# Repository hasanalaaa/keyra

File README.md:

<div align="center">

<a href="#readme">
  <picture>
    <source media="(prefers-color-scheme: dark)" srcset="docs/brand/readme/banner-dark.svg">
    
  </picture>
</a>

<h3>Your passwords stay on the device.<br>Keyra types them for you, only when you press its button.</h3>

<a href="https://hasanalaaa.github.io/keyra/">Website</a>&nbsp;&nbsp;·&nbsp;&nbsp;<a href="#how-it-works">How it works</a>&nbsp;&nbsp;·&nbsp;&nbsp;<a href="#quick-start">Quick start</a>&nbsp;&nbsp;·&nbsp;&nbsp;<a href="#security-model">Security</a>&nbsp;&nbsp;·&nbsp;&nbsp;<a href="#hardware">Hardware</a>&nbsp;&nbsp;·&nbsp;&nbsp;<a href="#faq">FAQ</a>&nbsp;&nbsp;·&nbsp;&nbsp;<a href="README.ar.md">العربية</a>
<br><br>

</div>

<picture>
  <source media="(prefers-color-scheme: dark)" srcset="docs/images/hero-dark.jpg">
  
</picture>
<p align="center"><sub>Concept render of a future enclosure. Today Keyra runs on a bare ESP32-S3 dev board: see <a href="#hardware">Hardware</a>.</sub></p>

---

<div dir="rtl">

## بالعربي

**Keyra** خزنة كلمات مرور صغيرة بحجم الـ USB، مبنية على لوحة ESP32-S3. تبقى كلماتك مشفّرة داخل الجهاز، وتديرها من متصفح هاتفك عبر شبكة الجهاز نفسه (`http://keyra.local`)، وعند الحاجة **يكتب Keyra اسم المستخدم وكلمة المرور** في الكمبيوتر كأنه لوحة مفاتيح، **ولكن فقط بعد أن تضغط زر الجهاز بيدك**. لا حساب، لا سحابة، لا إنترنت.

اقرأ الشرح كاملاً بالعربية: **[README.ar.md](README.ar.md)**

</div>

---

## Why Keyra

Most password managers live in the same computer and browser that attackers target. Keyra moves the secret somewhere else.

- **Your vault never lives on the computer.** Nothing is stored or synced there: the computer only sees a keyboard typing the one credential you chose, at the moment you chose. No clipboard, no app to install. (The optional browser extension only *asks* Keyra to type; it never holds a password.)
- **Malware cannot make it type.** Every action needs a physical press of the button on the device. No press, no typing.
- **No cloud, no account, no subscription.** The vault is encrypted on the device and managed over the device's own Wi-Fi. Nothing leaves your desk.
- **Works on any computer.** If it accepts a USB keyboard (a work laptop, a locked-down kiosk, a TV, a console), Keyra works there. Phones, tablets and computers without a free port can pair with it over Bluetooth. Nothing to install.
- **Open and cheap.** MIT licensed firmware for a development board that costs a few dollars. Read it, build it, change it.
- **Easy enough to use daily.** A phone-first app in Arabic and English, built to feel as simple as the password manager on your phone.

Keyra is a convenience-and-isolation device, not a magic shield. Read the [security model](#security-model) for exactly what it does and does not protect.

## How it works

<picture>
  <source media="(prefers-color-scheme: dark)" srcset="docs/brand/readme/how-it-works-dark.svg">
  
</picture>

https://github.com/user-attachments/assets/99ea60c0-720a-45a1-a4e3-737aead647fd

<p align="center"><sub>The press, 8 s: blue while it waits, green once it has typed. Concept render.</sub></p>

1. **Plug in.** Connect Keyra's USB port to the computer. It shows up as a keyboard. (Or pair it once over Bluetooth: see below.)
2. **Join the Wi-Fi.** On your phone, join the network **Keyra-XXXX** and open **http://keyra.local**. (No sign-in sheet pops up; see the [FAQ](#faq).)
3. **Pick an account and what to type.** Unlock with your master passphrase, tap an account, and choose **Username**, **Password**, **Both** or **Code** (2FA).
4. **Press the button.** Click the login field on your computer, press Keyra's button, and it types. The LED flashes green and your phone says **Typed**.

A long press (1.5 seconds) cancels a pending action, or locks the vault if nothing is pending.

```mermaid
sequenceDiagram
    autonumber
    participant P as Your phone
    participant K as Keyra
    participant C as Computer
    P->>K: Type the password of "GitHub" (Wi-Fi, keyra.local)
    Note over K: Armed for 60 s. LED breathes blue.
    Note over K: You press the button
    K->>C: Types it as a USB or Bluetooth keyboard
    K-->>P: Typed
    Note over C: The computer never sees the vault
```

**Bluetooth.** In **Device → Bluetooth**, tap **Pair a new device** and press Keyra's button. For the next 2 minutes Keyra shows up as a keyboard in your phone's, tablet's or computer's Bluetooth settings, and its light pulses cyan; pick it there. After that, **Type into: Auto** types over USB when Keyra is plugged in and otherwise into the Bluetooth device you used last (or pick one in the account sheet). Keyra connects to it only for the action, and the Ready screen tells you which device it is.

## Features

| | |
|---|---|
| **Types like a keyboard** | USB and Bluetooth keyboard. Handles Caps Lock and always releases keys, even on errors. |
| **Any input language** | Tell Keyra each computer's system once: on Windows it types character codes that ignore the active language; on a Mac or iPhone in Arabic it switches to English, types, and switches back. |
| **Updates over Wi-Fi** | **Device → Firmware update** checks GitHub for a new version and installs it after a press of Keyra's button. Only firmware signed with your key is accepted, never an older version, and a version that fails to start rolls back by itself. |
| **Passkeys and security key (USB)** | Keyra is also a FIDO2/U2F security key: create and use passkeys, or use it as a second factor, on sites that support security keys. Press the button when the light double-blinks white. Up to 50 passkeys, listed in **Security → Passkeys**. Optional security key PIN (set from the computer), `hmac-secret` and `credProtect`; passkeys travel in encrypted backups by default. Not FIDO certified; see [docs/FIDO.md](docs/FIDO.md). |
| **Browser extension (optional)** | Keyra Companion for Chrome 116+, Edge, Brave, Opera, Vivaldi and Firefox 128+: a Keyra key in login fields lists the logins for that site, warns before typing a login on another site, fills a strong password from Keyra in sign-up forms and offers **Save to Keyra?** afterwards. Connects with one press; never sees a stored password. See [extension/README.md](extension/README.md). |

<details>
<summary><b>All features</b> (activity log, password health, passkeys, NFC tags, recovery key, generator, import, backup and more)</summary>
<br>

| | |
|---|---|
| **Delete after typing** | Mark an account to delete itself after its password is typed once (or a set number of times): one-time recovery codes and temporary passwords clean themselves up. |
| **Activity log** | **Security → Activity** shows unlocks, wrong passphrase attempts, locks and why, what was typed and when, backups and more. Encrypted on Keyra, never a password, and it can't be cleared from the app. |
| **Password health** | **Security → Password health** lists reused, weak and year-old passwords. Keyra checks them itself; only the list of accounts reaches the phone, never a password. |
| **Bluetooth keyboard** | Bluetooth LE (HID over GATT) for phones, tablets and computers, with the same typing engine. Pairing only opens for 2 minutes after a button press; up to 4 devices; forget any of them from the app. |
| **Android app (optional)** | Keyra for Android (build it from `android/`): autofill suggestions that ask Keyra to type (you still press the button), **Save to Keyra**, and a password generator. It never receives a stored password. See [android/README.md](android/README.md). |
| **Access tokens and AI agents** | **Device → Apps and agents** makes revocable tokens for the Android app, the browser extension or an AI agent. A token can list account names and ask Keyra to type or save, never read a password, and every action still waits for your press. [`tools/keyra-mcp`](tools/keyra-mcp/README.md) lets an MCP client such as Claude Code log in this way. |
| **NFC tags** | **Device → NFC tags** makes stickers: tap one with your phone to get one account ready to type, then press Keyra's button. NTAG 424 DNA tags cannot be cloned. |
| **Recovery key** | Optional. **Security → Recovery kit** makes a key you can print or split into shares; it opens the vault again if you forget the passphrase. |
| **Reveal only after a press** | By default passwords, 2FA secrets and backups reach the phone only after you press Keyra's button, so a stolen browser session reads nothing. |
| **Lock when unplugged** | The vault locks about a second after the USB computer is unplugged or goes to sleep (on by default); optionally also when the Bluetooth device disconnects. |
| **Phone-first web app** | Installable to the home screen. Search, favorites, recents and a strength meter. |
| **Password generator** | Keyra makes new passwords with its hardware random generator: 8 to 128 characters, choose a–z / A–Z / 0–9 / symbols, minimum numbers and symbols, avoid look-alikes. Shows the exact strength in bits. Type it, type it twice (for "confirm password" fields), copy it, or save it. |
| **Password history** | Changing a password keeps the old one: the last 10, with dates, inside the encrypted account. Reveal or copy any of them. |
| **Type any text** | Keyra as a remote keyboard: type up to 256 characters (a Wi-Fi key, a one-off code) after a button press. Keyra forgets the text right after. |
| **Arabic and English** | Full RTL support, auto-detected, switchable at any time. |
| **2FA codes** | Built-in TOTP (SHA-1/256/512, 6 or 8 digits, 30 or 60 seconds). Keyra can type the code too. Add the key by pasting a setup key or `otpauth://` link, or with **Scan QR from a photo**. |
| **Encrypted vault** | PBKDF2-HMAC-SHA256 (about 1.2 s on the device) and per-entry AES-256-GCM. |
| **Unlock rate limiting** | Failed attempts are counted before the key derivation runs; power-cycling does not reset the delay. |
| **Import** | Move from Apple Passwords, Chrome, Bitwarden or 1Password CSV exports, or move 2FA keys from a Google Authenticator export QR. |
| **Encrypted backup** | A passphrase-protected JSON file (format version 3) with accounts, password history and, by default, passkeys; restore by merging or replacing. Older backup files still import. |
| **Physical confirmation** | Typing, passkey and security-key sign-ins, setup, Wi-Fi changes, Bluetooth pairing, firmware installs, saves from apps, deleting an account or passkey, changing the recovery key and factory reset all need a button press. |
| **Home Wi-Fi (optional)** | Keyra can join your home network so `keyra.local` opens from any device on it. Each new browser there is approved once with the button. |
| **Status LED** | Locked, ready, typing, success and error, readable at a glance. |
| **Auto-lock** | Locks after idle (1 to 120 minutes) and zeroizes keys in RAM. |
| **No lock-in** | Standard formats, open protocol ([docs/SPEC.md](docs/SPEC.md)), MIT license. |

</details>

## Screenshots

| Accounts | Ready: press the button | Typed | Security |
|:--:|:--:|:--:|:--:|
| <picture><source media="(prefers-color-scheme: dark)" srcset="web/screenshots/vault-en-dark.png"></picture> | <picture><source media="(prefers-color-scheme: dark)" srcset="web/screenshots/ready-en-dark.png"></picture> | <picture><source media="(prefers-color-scheme: dark)" srcset="web/screenshots/typed-en-dark.png"></picture> | <picture><source media="(prefers-color-scheme: dark)" srcset="web/screenshots/security-en-dark.png"></picture> |

| Type | Device | Search finds settings too | Typing to |
|:--:|:--:|:--:|:--:|
| <picture><source media="(prefers-color-scheme: dark)" srcset="web/screenshots/typing-en-dark.png"></picture> | <picture><source media="(prefers-color-scheme: dark)" srcset="web/screenshots/settings-en-dark.png"></picture> | <picture><source media="(prefers-color-scheme: dark)" srcset="web/screenshots/search-actions-en-dark.png"></picture> | <picture><source media="(prefers-color-scheme: dark)" srcset="web/screenshots/target-en-dark.png"></picture> |

Arabic (right-to-left) and English, light and dark, phone and desktop — all generated from the real app by `npm --prefix web run e2e` (every screen is in [web/screenshots](web/screenshots)).

## Security model

The short version. The full threat model, cryptographic design and rate-limit schedule are in **[SECURITY.md](SECURITY.md)**.

**What Keyra does**

- Encrypts every entry with AES-256-GCM under a random data key, itself protected by a key derived from your passphrase (PBKDF2-HMAC-SHA256, calibrated to about 1.2 s).
- Rate-limits unlock attempts and counts them durably.
- Types only after a physical button press. The computer never gets a storage or network channel from Keyra.
- Signs passkey and security-key requests only while unlocked and after a button press; passkey keys are encrypted with the vault key ([docs/FIDO.md](docs/FIDO.md)).
- Lets a new Bluetooth device pair only during a 2-minute window opened by a button press; the rest of the time only already-paired devices can even connect.
- Keeps decrypted data in RAM only while unlocked, and zeroizes it on lock. It also locks by itself when the USB computer is unplugged or sleeps.
- Shows passwords, 2FA secrets and backups on the phone only after a button press (**Protect reveal**, on by default), so a stolen browser session cannot read them. Deleting an account or passkey, and changing the recovery key, always need a press.
- Gives apps, the browser extension and AI agents arm-only tokens: they can ask Keyra to type or save, never read, and each action needs a press.
- Lets you set a recovery key (optional). Without one, a forgotten passphrase cannot be recovered; with one, it opens the vault again.

**What it does not do (honest limits)**

- **The phone link is plain HTTP over WPA2**, not TLS. Someone who knows your Keyra Wi-Fi password and is on the network can observe the traffic. Keep the Wi-Fi password private.
- **No secure element.** With physical access to the board, an attacker can dump the flash and guess your passphrase offline. Use a long passphrase.
- **Flash encryption and secure boot are optional** and off by default. They are irreversible eFuse steps ([docs/HARDWARE.md](docs/HARDWARE.md#optional-hardening-irreversible)).
- **Keyra has not been independently audited.**
- A keylogger on the computer can still see what Keyra types, as with any keyboard.
- **The security key is not FIDO certified** and uses self attestation; without a secure element its keys are as safe as your passphrase. Unless you set a security key PIN (from the computer), "user verification" means Keyra is unlocked, not a PIN or fingerprint for each sign-in.
- **Bluetooth pairing is "Just Works"** (Keyra has no screen to show a code). Someone within radio range during the 2-minute pairing window could pair their own device, or try to sit in the middle of yours. Pair where you can see who is around, and check the device list afterwards. Details in [SECURITY.md](SECURITY.md#bluetooth).

If you need to report a vulnerability, please use a **private GitHub Security Advisory** as described in [SECURITY.md](SECURITY.md#reporting-a-vulnerability).

## Hardware

<p align="center"><sub>Concept render. The board you can build today is described below.</sub></p>

Keyra runs on a stock **ESP32-S3** dev board with at least **8 MB flash**. No soldering.

| | |
|---|---|
| **Reference board** | ESP32-S3-DevKitC-1 **N16R8** (PSRAM is optional) |
| **Button** | GPIO0 (the board's **BOOT** button) |
| **Status LED** | WS2812 on **GPIO38** (DevKitC-1 v1.1) or **GPIO48** (v1.0), set with `CONFIG_KEYRA_LED_GPIO` |
| **USB** | Plug the board's native **USB** port into the computer (not the UART port) |

Pin details, flashing options and the optional hardening steps: **[docs/HARDWARE.md](docs/HARDWARE.md)**.

### Enclosure

A printable case for the dual USB-C YD-ESP32-S3 board: five parts, a big mechanical button that presses the board's own BOOT switch, a clear ring that carries the LED's light around it, and the Contour debossed in the lid. No screws, no extra electronics. Cable and USB-C dongle versions, the parametric OpenSCAD source and print settings: **[hardware/enclosure](hardware/enclosure)**.

## Quick start

### Option A: flash a prebuilt release

1. Download the release files from the [Releases page](https://github.com/hasanalaaa/keyra/releases): `bootloader.bin`, `partition-table.bin`, `ota_data_initial.bin`, `keyra-firmware.bin`, `flash-offsets.txt` and `SHA256SUMS`.
2. Put the board in download mode (hold **BOOT**, plug in the **USB** port, release **BOOT**), or use the **UART** port, which needs no button.
3. Flash with [esptool](https://docs.espressif.com/projects/esptool/en/latest/) (the offsets are in `flash-offsets.txt`, one of the release files):

```sh
esptool.py --chip esp32s3 -p <PORT> --before default-reset --after hard-reset \
  write_flash --flash-mode dio --flash-size 8MB --flash-freq 80m \
  0x0 bootloader.bin 0x8000 partition-table.bin 0xf000 ota_data_initial.bin 0x20000 keyra-firmware.bin
```

That is needed once. After it, **Device → Firmware update** installs new versions over Wi-Fi (Keyra on your home network): it checks the [Releases page](https://github.com/hasanalaaa/keyra/releases), downloads, verifies the signature and installs after a press of Keyra's button.

### Option B: build from source

You need [ESP-IDF 6.0.x](https://docs.espressif.com/projects/esp-idf/en/stable/esp32s3/get-started/) installed and exported in your shell (CI uses v6.0.2).

```sh
git clone https://github.com/hasanalaaa/keyra.git
cd keyra/firmware

# Release build: plain keyboard, logging off. Recommended for daily use.
idf.py -B build-release -D SDKCONFIG_DEFAULTS="sdkconfig.defaults;sdkconfig.release" build
idf.py -B build-release -p <PORT> flash

# Dev build: adds a USB serial log port and the 1200-baud reboot-to-ROM hook.
idf.py build
idf.py -p <PORT> flash monitor
```

The built web app is committed in `firmware/components/keyra_api/www/`, so you do **not** need Node.js to build the firmware. To rebuild the web app and refresh those files:

```sh
npm --prefix web ci && npm --prefix web run build
```

### First-time setup

1. Plug Keyra's **USB** port into a computer.
2. On your phone, join Wi-Fi **Keyra-XXXX** (the last four characters of the board's address). The factory password is **`keyra1234`**, and it is public. Setup makes you change it.
3. Open **http://keyra.local** (or `http://192.168.4.1`). Tap **Share, then Add to Home Screen** to make it one tap next time.
4. Follow the three steps: choose a **master passphrase** (10 characters or more; longer is better), choose a **new Wi-Fi password**, then **press the button on Keyra** to prove you are holding it.
5. Add accounts, or import a CSV from your current password manager (delete the CSV afterwards, it is unencrypted).

### Home Wi-Fi (optional)

Keyra can also join your home network, so you can open it from any phone or laptop at home without switching Wi-Fi.

1. In **Device → Home Wi-Fi**, turn on **Use home Wi-Fi** and pick your network. Keyra only joins password-protected (WPA2/WPA3) networks.
2. Enter the network's password, tap **Join**, then **press Keyra's button**. The sheet shows **Connected**, Keyra's address on your network and the signal strength.
3. From any device on that network, open **http://keyra.local**. If a device cannot resolve `.local` names, use the address shown in the sheet.
4. The first time each browser unlocks Keyra through the home network, Keyra asks you to **press its button to trust that browser**. Trusted browsers (up to 8) are listed in **Device → Trusted browsers**, where you can remove them. Removing one signs it out.

### Updating

1. Join Keyra to your home Wi-Fi (see above): checking for updates needs the internet.
2. Open **Device → Firmware update** and tap **Check for updates**.
3. If a newer version is listed, tap **Download and install**, then **press Keyra's button** when the sheet asks. Keyra restarts with the new version; unlock it again.

Your accounts stay as they are (the vault has its own storage). Keyra accepts only firmware signed with your release key, never an older version, and if the new version fails to start it goes back to the previous one by itself. Without home Wi-Fi, **Install from a file** takes a downloaded `keyra-firmware.bin`.

### New password for a website

1. On the website's sign-up or change-password page, open Keyra's **Type** tab and tap **Generate password**. Keyra makes a password (20 characters by default; the sheet remembers your settings in this browser).
2. Click the website's first password field, tap **Type twice**, then **press Keyra's button**. Keyra types the password, presses Tab, and types it again into the confirm field.
3. Tap **Save**: **New account** opens a filled-in form, or **Update an account** replaces that account's password. The old password stays in the account's **Password history**.

To type something that isn't saved in Keyra, open the **Type** tab, then **Type text**, enter up to 256 characters, tap **Type it** and press the button. **Type it twice** can put a Tab or an Enter between the two copies.

**Keep Keyra's own Wi-Fi on** is on by default. Turn it off and Keyra's own Wi-Fi switches off about 15 seconds after Keyra joins your home network; it comes back if the home network has been unavailable for 60 seconds, or 30 seconds after power-up if Keyra has not joined by then, so Keyra stays reachable. Keyra has one radio: its own Wi-Fi moves to your home network's channel, and phones joined to it may reconnect once. While home Wi-Fi is connected, Keyra sets its clock from the internet (NTP), so 2FA codes work without a phone having set the time.

### NFC tags

Stick an NFC tag on your desk; tapping it with your phone gets one account ready to type, and you press Keyra's button. The phone must be on Keyra's network (its own Wi-Fi or your home network), and Keyra must be unlocked.

1. In **Device → NFC tags**, tap **New tag**, pick the account, what to type and **Any NFC tag**, tap **Create tag** and press Keyra's button.
2. On iPhone, open **NFC Tools → Write → Add a record → URL**, paste the link Keyra shows (once), tap **Write** and hold the tag near the top of the phone. NXP TagWriter works too.
3. Tap the tag: Safari opens a small Keyra page that says **Press Keyra's button**. Press it and Keyra types.

Anyone who copies a simple tag's link can ask Keyra to type that account (never see it), so your press is still the check. An **NTAG 424 DNA** tag can't be copied: choose it in step 1 and set the keys and SDM offsets Keyra shows in NXP TagWriter. Details: [docs/research/NFC-TAGS.md](docs/research/NFC-TAGS.md).

### Browser extension

1. Build it (`npm --prefix extension ci && npm --prefix extension run build`) and load `extension/dist/chrome` in `chrome://extensions` (Developer mode → **Load unpacked**; Chrome 116+, Edge, Brave, Opera and Vivaldi), or `extension/dist/firefox` in Firefox 128+'s `about:debugging`. Safari is not shipped.
2. Click the Keyra button in the toolbar, enter Keyra's address and click **Connect**. A Keyra tab opens: unlock, tap **Create token** and **press Keyra's button**. The tab closes by itself.
3. On a website, click into the login field and then the small Keyra key: pick the login and **press Keyra's button**. After a sign-up or a password change, the extension asks **Save to Keyra?** or **Update the password?** — again a press.

Only logins for the page's own site are offered; choosing one for another site shows a warning that names both. Install, privacy and permissions: [extension/README.md](extension/README.md).

## Project layout

```
keyra/
├── firmware/                  ESP-IDF 6.0 project (C++17)
│   ├── main/                  app_main: wiring only
│   ├── components/
│   │   ├── keyra_vault/       crypto, encrypted storage, TOTP, backup (host-tested)
│   │   ├── keyra_hid/         typing engine over USB (TinyUSB) or Bluetooth, dev CDC port
│   │   ├── keyra_ble/         Bluetooth LE keyboard (NimBLE, HID over GATT), pairing and bonds
│   │   ├── keyra_fido/        USB security key: CTAPHID, CTAP2 + U2F, passkeys (host-tested)
│   │   ├── keyra_io/          button (GPIO0) and RGB status LED
│   │   ├── keyra_net/         Wi-Fi access point, DNS, mDNS (keyra.local)
│   │   └── keyra_api/         HTTP server, REST API, sessions, pending-action state machine
│   ├── test/host/             host test runner (CMake + ctest, no board needed)
│   ├── partitions.csv         8 MB layout: 2 app slots + LittleFS vault
│   └── sdkconfig.defaults / sdkconfig.release   dev and release profiles
├── web/                       Preact + TypeScript app, built into one gzipped file
├── android/                   Keyra for Android: autofill and save through access tokens (Kotlin)
├── extension/                 Keyra Companion: browser extension (Manifest V3; Chrome, Edge, Brave, Opera, Vivaldi, Firefox)
├── tools/
│   ├── keyra-mcp/             MCP server: lets an AI agent ask Keyra to type a login
│   ├── release.sh             build, sign and publish a release
│   ├── sign_release.sh        sign a firmware image for network updates
│   ├── ci_local.sh            the CI jobs, run locally
│   └── devctl.py, fido_harness.py   flash/reset/log; python-fido2 vs. the FIDO core
├── docs/                      SPEC.md, DESIGN.md, HARDWARE.md, FIDO.md, IMAGE_PROMPTS.md, images/
│   ├── brand/                 logo, colours, type and motion (BRAND.md), README art
│   └── research/              design notes: tokens, NFC tags, host matching, passkey backup, roadmap
└── .github/                   CI, issue and PR templates
```

[docs/SPEC.md](docs/SPEC.md) is the contract between firmware and web app (REST API, behavior, security model). [docs/DESIGN.md](docs/DESIGN.md) is the design system.

## Development

```sh
# Host tests: vault, TOTP, key map, action state machine, FIDO core. No board needed.
# Requires CMake, a C++17 compiler and OpenSSL 3 headers (libssl-dev, or openssl@3 on Homebrew).
cmake -S firmware/test/host -B build/host && cmake --build build/host && ctest --test-dir build/host

# The FIDO core against python-fido2's client and server (fake HID link, no board)
python3 -m venv .venv && .venv/bin/pip install fido2
.venv/bin/python tools/fido_harness.py build/host/keyra_fido/fido_harness

# Web: typecheck and unit tests
npm --prefix web ci
npm --prefix web run typecheck
npm --prefix web test

# Web UI without a board: a mock of the device API (demo passphrase: keyra demo vault)
npm --prefix web run mock

# End-to-end run in a headless browser (Playwright); regenerates the screenshots
npm --prefix web run e2e

# Browser extension: typecheck, unit tests, build, and an end-to-end run in Chromium
npm --prefix extension ci
npm --prefix extension run typecheck && npm --prefix extension test && npm --prefix extension run build
npm --prefix extension run e2e
```

CI runs the host tests, the web checks and both firmware profiles on every push and pull request; `tools/ci_local.sh` runs the same jobs locally. See [CONTRIBUTING.md](CONTRIBUTING.md).

## Roadmap

Ideas, not promises. Priorities follow what real users on real boards report.
The current work plan, with what is done and what comes next, is in [docs/research/ROADMAP.md](docs/research/ROADMAP.md).

- [x] 0.1: encrypted vault, USB typing, phone app (EN/AR), TOTP, import, backup, CI
- [x] 0.2.0: Bluetooth LE keyboard, USB passkeys / FIDO2 + U2F security key, over-the-air firmware updates (signed, with rollback)
- [x] 0.3.0: security key PIN (ClientPIN, separate from the master passphrase), `hmac-secret` and `credProtect`, passkeys in encrypted backups (format version 3)
- [x] 0.3.0: Android app, Keyra Companion browser extension, access tokens and the agent gate (`tools/keyra-mcp`), NFC tap tags
- [x] Board matrix and a prebuilt image for each of seven boards (0.4.5; [docs/HARDWARE.md](docs/HARDWARE.md); hardware-tested so far: YD-ESP32-S3)
- [x] Browser-based flashing for every board from [the website](https://hasanalaaa.github.io/keyra/)
- [x] Printable enclosure ([hardware/enclosure](hardware/enclosure))
- [x] A purpose-built PCB, designed and ready to order: [Keyra Stick](hardware/pcb/keyra-stick) (not yet built)
- [ ] Independent security review (an internal review and its fixes shipped in 0.4.5: [docs/research/SECURITY-REVIEW-2026-10.md](docs/research/SECURITY-REVIEW-2026-10.md))

## FAQ

<details>
<summary><b>Why doesn't my phone show a "sign in to Wi-Fi" popup?</b></summary>

On purpose. Keyra answers your phone's connectivity checks as "online" so the phone joins like any normal network and does not open a cramped captive-portal sheet (which often cannot run the app properly or keep cookies). Just open **http://keyra.local** in your regular browser. If that name does not resolve, use `http://192.168.4.1`.

</details>

<details>
<summary><b>My computer is in Arabic (or another language). Will Keyra type the right characters?</b></summary>

Yes, once Keyra knows the computer's system (Device → Keyboard, Device → Bluetooth per device; iPhones, iPads and Macs are recognised when they pair). On **Windows** it types each character as an Alt code, which comes out the same in every input language. On a **Mac, iPhone or iPad**, set "Its language now" to Arabic under "Type into": Keyra presses Ctrl+Space to switch to English, types, and switches back. On **Android**, set the physical keyboard "Keyra" to English (US) once. No keyboard can *read* a computer's language, which is why Apple hosts need that one tap. Characters a layout cannot type are refused with a clear message, never typed wrong.

</details>

<details>
<summary><b>Can Keyra type into my phone or tablet?</b></summary>

Yes, over Bluetooth. Pair it once from **Device → Bluetooth** (see [How it works](#how-it-works)). iPhone and iPad hide their on-screen keyboard while any Bluetooth keyboard is connected, so by default (**Connect: When typing**, recommended) Keyra connects only for each action: it shows "Connecting to your device…" for a moment, types after your press, and lets go about 20 seconds later. Choose **Always** if you prefer instant typing and do not mind the hidden on-screen keyboard. The account sheet's **Type into** picker chooses USB or a paired device; this browser remembers the choice.

</details>

<details>
<summary><b>I forgot my master passphrase. Can I recover my passwords?</b></summary>

Only with a recovery key you made earlier (**Security → Recovery kit**; make one while you still remember the passphrase). On the unlock screen choose **Use recovery key**, enter it and pick a new passphrase. Without a recovery key, no: that is the point of encryption, and there is no backdoor. You can **erase the device and start over**: on the unlock screen choose **Forgot passphrase?**, then press Keyra's button to confirm. All accounts are deleted. Restore from a backup if you have one.

</details>

<details>
<summary><b>Is it safe to type a password with a button press? What if the wrong window is focused?</b></summary>

The action is armed for 60 seconds and runs once on the press. Click the right field first. A long press cancels.

</details>

<details>
<summary><b>Why HTTP and not HTTPS?</b></summary>

A device on its own network cannot get a certificate that browsers trust without installing something on each phone, and a browser warning teaches people to ignore warnings. The link is protected by WPA2 and a private Wi-Fi password instead. This is a real limit: see [SECURITY.md](SECURITY.md).

</details>

<details>
<summary><b>Can I add a 2FA key from a QR code?</b></summary>

Yes. In the account form, tap **Scan QR from a photo**, then take a photo of the QR or choose a saved picture. The picture is decoded inside your phone's browser; it is never sent to Keyra or anywhere else. Keyra's page is plain HTTP, so browsers do not allow a live camera view there, hence the photo. Plain `otpauth://totp/…` QR codes fill the 2FA field (and the name and user name if they are empty). For Google Authenticator, use **Import**, then **Google Authenticator export**: it lists the accounts in the export QR (several QR codes for big exports, one scan each) and either adds them as new accounts or adds the key to existing accounts that match by name and user name. Keyra only makes time-based codes, so counter-based (HOTP) entries, MD5 and unusual digit counts or periods are rejected or skipped with a message. Delete any photo or screenshot of the QR afterwards: it holds your keys unencrypted.

</details>

<details>
<summary><b>Do I need an internet connection?</b></summary>

No. Keyra creates its own Wi-Fi network, and your phone does not need internet while connected to it (it may keep using mobile data for other apps). If you turn on home Wi-Fi, Keyra uses the internet, on your home network only, for the time (NTP) and to check for and download firmware updates from GitHub when you ask it to, and for nothing else; your vault never leaves the device.

</details>

<details>
<summary><b>Do I still need Keyra's own Wi-Fi once home Wi-Fi works?</b></summary>

Not for everyday use at home: open http://keyra.local on your home network instead. Keyra's own Wi-Fi is still useful. It is how you set Keyra up and how you reach it when the home network is down (with **Keep Keyra's own Wi-Fi on** turned off, it comes back after a minute without the home network). It is also the safer way to unlock on a network you do not fully trust, because traffic on it is visible only to devices that know Keyra's Wi-Fi password (see [SECURITY.md](SECURITY.md#home-wi-fi-optional)). If you never want it while at home, turn **Keep Keyra's own Wi-Fi on** off.

</details>

<details>
<summary><b>Can the computer read my vault?</b></summary>

Keyra presents a keyboard and a security key to the computer. It has no storage interface and no network path to it. The computer sees what gets typed, and it can ask the security key to sign a website's challenge, which needs your button press; it can never read the vault or a key. Over Bluetooth a paired device sees a keyboard, Keyra's name and maker, and a battery level, nothing more.

</details>

<details>
<summary><b>Is Keyra a YubiKey replacement?</b></summary>

No. Keyra can create and use passkeys and act as a security key over USB, and for many personal accounts that works well. But a YubiKey keeps its keys in a secure chip that cannot be read out, is FIDO certified, asks for its PIN on every sign-in, and works over NFC. Keyra has no secure chip (its keys are as safe as your passphrase and the flash encryption setting), is not certified, treats "unlocked" as user verification unless you set an optional security key PIN, and works only by USB (phones need a USB connection). Some sites, mostly corporate ones, refuse uncertified keys. Register a second key or keep another sign-in method on every account. Details in [docs/FIDO.md](docs/FIDO.md).

</details>

<details>
<summary><b>Which passkey sites work?</b></summary>

Any site that accepts a USB security key or "passkey on a security key", in Chrome, Edge, Safari or Firefox on macOS, Windows and Linux. Passkeys need Keyra plugged in and unlocked; keep the phone app handy to unlock it. Encrypted backups carry the passkeys too (Security → "Passkeys in backups", on by default), so a restored Keyra signs in where the old one did.

</details>

<details>
<summary><b>What does it cost?</b></summary>

A compatible ESP32-S3 board is usually a few dollars to about ten.

</details>

## Contributing

Bug reports, hardware test reports, translations and pull requests are welcome. Start with [CONTRIBUTING.md](CONTRIBUTING.md) and the [Code of Conduct](CODE_OF_CONDUCT.md). For security issues, use a private advisory ([SECURITY.md](SECURITY.md)).

## License

[MIT](LICENSE) © 2026 hasanalaaa. Third-party components keep their own licenses (ESP-IDF, TinyUSB, LittleFS, cJSON, Preact). The app and the wordmark use [Readex Pro](https://fonts.google.com/specimen/Readex+Pro) (SIL OFL 1.1). Logo and brand: [docs/brand/BRAND.md](docs/brand/BRAND.md).

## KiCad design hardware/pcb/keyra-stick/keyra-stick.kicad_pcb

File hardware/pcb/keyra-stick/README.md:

# Keyra Stick

Keyra's own board: a 0.8 mm USB-C stick that plugs straight into a computer. One big button, a
ring of eight RGB LEDs around it, the ESP32-S3 module at the far end. Open hardware (MIT), ready to
order fully assembled from JLCPCB with the files in [fab/](fab).

**The illustrated guide** walks through every part, the size, how it works, the schematic, the parts
list, ordering and first power-up: [English](docs/keyra-stick-guide-en.pdf) ·
[العربية](docs/keyra-stick-guide-ar.pdf) (PDF).

> **Status: designed and checked, not yet built.** The schematic passes KiCad's electrical rules
> check, the board passes the design rules check with zero errors and matches the schematic
> exactly, and every fab file is rebuilt from one description by `gen/build.sh`. No board has been
> manufactured or powered yet: if you build one, please report how it went.

## At a glance

| | |
|---|---|
| Size | 53.1 × 18.5 mm board plus the USB-C plug; about 3.2 mm thick with parts (the 2.4 mm module on a 0.8 mm board) |
| Board | 4 layers, 0.8 mm, ENIG, black mask, white silkscreen |
| Layers | top: parts and signals · In1: solid ground · In2: 3.3 V · bottom: signals and ground |
| Module | ESP32-S3-MINI-1-N8 (8 MB flash, no PSRAM); its PCB antenna at the board end with no copper under it on any layer |
| USB | USB-C plug, USB 2.0 full speed on the ESP32-S3's own USB; 5.1 kΩ Rd on CC; USBLC6-2SC6 ESD protection |
| Power | AP2112K-3.3 (600 mA) for the module; the LED ring on 5 V through a load switch on GPIO7 |
| Button | 5.1 mm tactile switch on GPIO5 (the chip's own pull-up): never a boot pin |
| Light | 8 × SK6805-EC20 (WS2812 protocol) on GPIO6 through an SN74LV1T125, for a clean 5 V data swing |
| Recovery | BOOT jumper (two pads) on the back: short it while plugging in for USB download mode |
| Firmware | the `keyra-stick` board profile: releases ship `keyra-firmware-keyra-stick.bin` |

Parts cost about US$6.7 per board at single-piece LCSC prices (November 2026: module 4.75, eight
LEDs 0.88, everything else under 1). JLCPCB adds the board, assembly, and a one-off loading fee per
"extended" part type; its quote gives the real total.

## Ordering from JLCPCB

1. Open [jlcpcb.com](https://jlcpcb.com) → **Order now** → **Add gerber file** →
   `fab/keyra-stick-gerbers.zip`.
2. PCB options:
   - **Layers: 4**, **PCB thickness: 0.8 mm**: the USB-C plug clamps a 0.8 mm board, nothing
     else fits.
   - **Surface finish: ENIG**: flat pads for the 0.5 mm-pitch plug and the 2 × 2 mm LEDs, and the
     gold mark on the back.
   - **PCB colour: black**, silkscreen white (any colour works).
   - Impedance control: not needed (USB full speed over a few centimetres).
   - **Mark on PCB / order number: "Specify a location"**, so it lands on `JLCJLCJLCJLC` on the back.
3. Turn on **PCB Assembly**: **Standard** (the plug is a "Standard only" part), **Top side**. Add
   a remark: *"J1 straddles the 0.8 mm edge: please solder its bottom-row pads too if possible.
   Edge rails on the long sides only, nothing at the USB-C end (the plug overhangs it)."*
4. Upload `fab/bom.csv` as the BOM and `fab/cpl.csv` as the placement file. Every line should
   match an LCSC part in stock; if a part is out of stock, the BOM's LCSC number names the exact
   part to substitute.
5. In the placement preview check the plug's pins sit on the pads at the tip, the module's pin-1
   dot is at its corner nearest the antenna end, and the eight LEDs all turn the same way round the ring.
   The footprints come from LCSC's own data, so nothing should need rotating.
6. Order.

The plug straddles the board. Its top row carries everything USB 2.0 needs; the bottom row only
repeats VBUS and ground, so the stick works even if that row is left unsoldered (it adds strength).

## First power-up

1. Look at the plug under a light: no solder bridges between its pins.
2. Short the BOOT jumper on the back (tweezers across its two pads), plug the stick in, then let go.
   The ESP32-S3's USB download port appears.
3. Install Keyra from the [browser installer](https://hasanalaaa.github.io/keyra/), choosing
   **Keyra Stick**, or with `esptool` and the files of a release (offsets in its
   `flash-offsets.txt`; the app image is `keyra-firmware-keyra-stick.bin`).
4. Unplug and plug in again: the ring breathes amber (setup). Continue with Keyra's normal setup.
   Later updates arrive over the air like on any other board.

Test points on the back, for bring-up or a pogo-pin jig: `5V`, `3V3`, `GND`, `EN` (short to
ground: reset), `IO0`, and the UART console `TX`/`RX` (115200 baud).

## Files

| Path | What it is |
|---|---|
| `keyra-stick.kicad_pro`, `.kicad_sch`, `.kicad_pcb`, `.kicad_dru` | KiCad 10 project: schematic, routed board, design rules |
| `fab/keyra-stick-gerbers.zip` | Gerbers (all four copper layers) and drill files |
| `fab/bom.csv`, `fab/cpl.csv` | JLCPCB's bill of materials and placement file |
| `docs/keyra-stick-guide-en.pdf`, `-ar.pdf` | The illustrated guide, in English and Arabic |
| `fab/keyra-stick-schematic.pdf` | The schematic, readable without KiCad |
| `fab/keyra-stick.stpZ` | 3D model of the assembled board (compressed STEP; KiCad and FreeCAD open it), for enclosures |
| `renders/` | Top, back and angled renders |
| `lib/` | Footprints and 3D models of the LCSC parts (from LCSC/EasyEDA data); their schematic symbols, drawn by `gen/symbols.py` |
| `gen/` | The generator: `design.py` holds every part, net and position; everything else is built from it, the guide included (`make_guide.py`, words in `guide_text.py`) |

## Changing the board

Edit `gen/design.py`, then run `gen/build.sh`. It draws the schematic, places the board (nets from
the schematic's own netlist), drops a via from every ground and 3.3 V pad into its plane, routes the
rest with Freerouting, fills the planes, runs the electrical check and the design rules check with
board-to-schematic parity, and writes every fab file and render. It needs KiCad 10, Java 21 and
Freerouting 2.1: `FREEROUTING=/path/to/freerouting-2.1.0.jar gen/build.sh`. After editing the board
by hand in KiCad, `gen/build.sh fab` re-checks it and re-exports the fab files only. Both end by
printing the guide with Google Chrome (`CHROME` overrides its path).

## Design notes

- **Antenna.** The module's antenna is flush with the board end and nothing is under it on any
  layer (Espressif's PCB layout guide). Keep metal away from that end in an enclosure.
- **Thin.** The plug sets the board at 0.8 mm (SHOU HAN DWG001-A401, "Cable Side PCB Layout"), and
  the tongue follows that drawing: 6.10 mm wide for 0.90 mm at the tip, then 7.90 mm to 6.30 mm.
- **USB.** Full speed (12 Mbit/s) edges take about 4 ns; traces of a few centimetres are far below
  the length where the pair's impedance matters, so they are routed short rather than as an
  impedance-controlled pair. The top layer sits on the solid ground plane.
- **Inrush.** At plug-in VBUS sees about 5 µF directly (USB 2.0 allows 10 µF), plus the 3.3 V
  rail's capacitors charged through the LDO's current limit. The ring's 5.5 µF waits behind its
  switch, which turns on over about a millisecond once the firmware drives GPIO7.
- **Heat.** The LDO drops 1.7 V: about 0.2 W at Keyra's typical 120 mA, more during Wi-Fi bursts,
  spread into the planes.
- **Beside the module.** The 18.5 mm width leaves a strip on each side of the module: its EN
  reset RC sits right at pin 45 and 4.7 µF + 100 nF right at its 3V3 pin, as Espressif asks.
- **Boot.** GPIO0 keeps the chip's own pull-up (normal boot); only the BOOT jumper selects
  download mode, so the main button can never start the board in the wrong mode.

---

<div dir="rtl">

## بالعربي

**Keyra Stick** هي لوحة Keyra الخاصة: عصا رفيعة بسمك 0.8 ملم تنشك مباشرة بمنفذ USB-C بالكمبيوتر.
بيها زر كبير بالنص وحوله حلقة من 8 أضواء ملونة، والرقاقة بنهاية العصا. التصميم مفتوح المصدر،
وجاهز ينطلب مركّب بالكامل من مصنع JLCPCB بملفات مجلد [fab](fab).

**الدليل المصوّر** يشرح كل قطعة، والمقاس، وطريقة العمل، والمخطط، وقائمة القطع، وطريقة الطلب، وأول تشغيل:
[بالعربي](docs/keyra-stick-guide-ar.pdf) · [English](docs/keyra-stick-guide-en.pdf).

**الحالة:** التصميم مكتمل ومفحوص: المخطط نجح بالفحص الكهربائي، واللوحة نجحت بفحص قواعد التصنيع بدون
أي خطأ وتطابق المخطط تماماً. بس بعد ما انصنعت ولا جُرّبت أي لوحة.

**طريقة الطلب:**
1. ادخل على موقع jlcpcb.com، وارفع ملف التصنيع `fab/keyra-stick-gerbers.zip`.
2. اختار: **4 طبقات**، و**سمك 0.8 ملم** (لازم، لأن رأس الـ USB-C ما يركب على غيره)، وتشطيب **ENIG**، واللون أسود.
3. شغّل **التجميع** (PCB Assembly): نوع **Standard**، والوجه العلوي.
4. ارفع `fab/bom.csv` (قائمة القطع) و`fab/cpl.csv` (أماكن القطع)، وتأكد كل القطع موجودة بالمخزن.
5. بالمعاينة تأكد: أرجل الرأس على وساداتها، ونقطة الرقاقة بالزاوية القريبة من نهاية الهوائي، والأضواء كلها بنفس الاتجاه.
6. اطلب.

**بعد ما توصلك:** وصّل نقطتي BOOT اللي ورا اللوحة بملقط وانت تشكها بالكمبيوتر، وثبّت Keyra من موقع المشروع
واختار **Keyra Stick**. بعدها كل التحديثات توصل عادي من «الجهاز ← تحديث البرنامج».

</div>

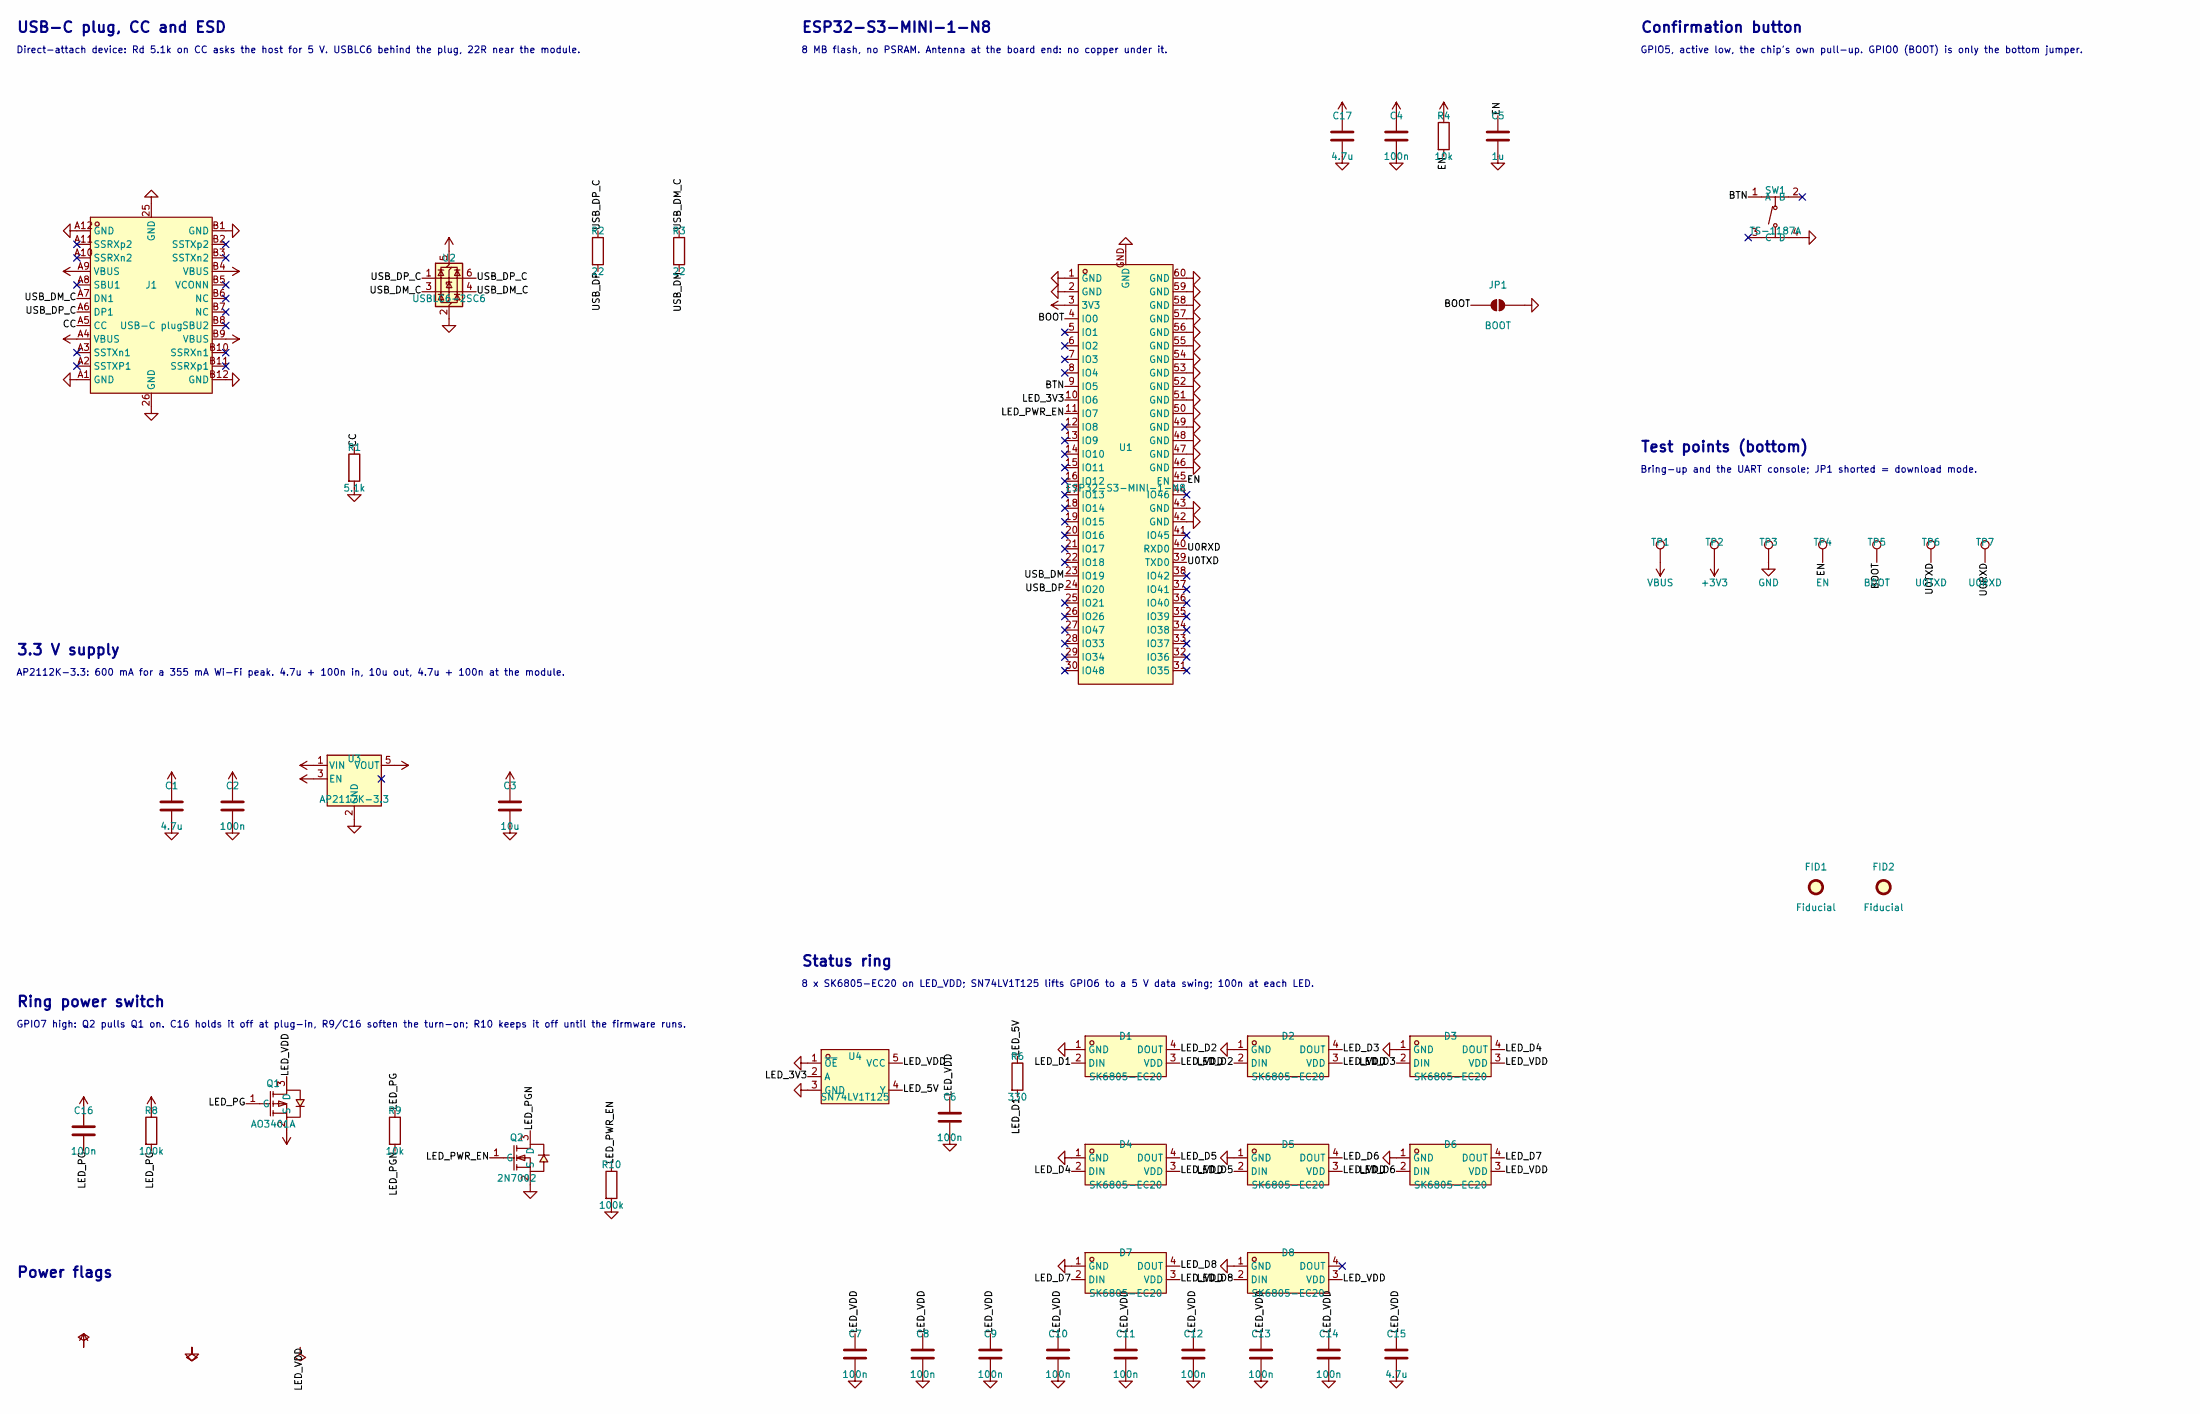
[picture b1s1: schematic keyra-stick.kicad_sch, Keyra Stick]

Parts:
C1, C15, C17: 4.7u; C_0603_1608Metric; LCSC C19666
C2, C4, C6, C7, C8, C9, C10, C11, C12, C13, C14, C16: 100n; C_0402_1005Metric; LCSC C1525
C3: 10u; C_0603_1608Metric; LCSC C19702
C5: 1u; C_0402_1005Metric; LCSC C52923
D1, D2, D3, D4, D5, D6, D7, D8: SK6805-EC20; LED-SMD_4P-L2.0-W2.0-TL_J-ST2020RGB-IC-P4-5-SO1; LCSC C2890036
FID1, FID2: Fiducial; Fiducial_0.75mm_Mask1.5mm
J1: USB-C plug; USB-C-SMD_TYPE-C-24P-GTJB-040; LCSC C3151751
JP1: BOOT; SolderJumper-2_P1.3mm_Open_RoundedPad1.0x1.5mm
Q1: AO3401A; SOT-23_L2.9-W1.3-P1.90-LS2.4-BR; LCSC C15127
Q2: 2N7002; SOT-23-3_L2.9-W1.3-P1.90-LS2.4-BR; LCSC C8545
R1: 5.1k; R_0402_1005Metric; LCSC C25905
R2, R3: 22; R_0402_1005Metric; LCSC C25092
R4, R9: 10k; R_0402_1005Metric; LCSC C25744
R6: 330; R_0402_1005Metric; LCSC C25104
R8, R10: 100k; R_0402_1005Metric; LCSC C25741
SW1: TS-1187A; SW-SMD_4P-L5.1-W5.1-P3.70-LS6.5-TL_H1.5; LCSC C318884
TP1: VBUS; TestPoint_Pad_D1.0mm
TP2: +3V3; TestPoint_Pad_D1.0mm
TP3: GND; TestPoint_Pad_D1.0mm
TP4: EN; TestPoint_Pad_D1.0mm
TP5: BOOT; TestPoint_Pad_D1.0mm
TP6: U0TXD; TestPoint_Pad_D1.0mm
TP7: U0RXD; TestPoint_Pad_D1.0mm
U1: ESP32-S3-MINI-1-N8; BULETM-SMD_ESP32-S3-MINI-1-N8; LCSC C2913206
U2: USBLC6-2SC6; SOT-23-6_L2.9-W1.6-P0.95-LS2.8-BL; LCSC C7519
U3: AP2112K-3.3; SOT-25-5_L2.9-W1.6-P0.95-LS2.8-BL; LCSC C51118
U4: SN74LV1T125; SOT-23-5_L3.0-W1.7-P0.95-LS2.8-BL; LCSC C473338

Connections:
+3V3: C3.1, C4.1, C17.1, R4.1, TP2.1, U1.3 (3V3), U3.5 (VOUT)
/BOOT: JP1.1 (A), TP5.1, U1.4 (IO0)
/BTN: SW1.1 (A), U1.9 (IO5)
/CC: J1.A5 (CC), R1.1
/EN: C5.1, R4.2, TP4.1, U1.45 (EN)
/LED_3V3: U1.10 (IO6), U4.2 (A)
/LED_5V: R6.1, U4.4 (Y)
/LED_D1: D1.2 (DIN), R6.2
/LED_D2: D1.4 (DOUT), D2.2 (DIN)
/LED_D3: D2.4 (DOUT), D3.2 (DIN)
/LED_D4: D3.4 (DOUT), D4.2 (DIN)
/LED_D5: D4.4 (DOUT), D5.2 (DIN)
/LED_D6: D5.4 (DOUT), D6.2 (DIN)
/LED_D7: D6.4 (DOUT), D7.2 (DIN)
/LED_D8: D7.4 (DOUT), D8.2 (DIN)
/LED_PG: C16.2, Q1.1 (G), R8.2, R9.1
/LED_PGN: Q2.3 (D), R9.2
/LED_PWR_EN: Q2.1 (G), R10.1, U1.11 (IO7)
/LED_VDD: C6.1, C7.1, C8.1, C9.1, C10.1, C11.1, C12.1, C13.1, C14.1, C15.1, D1.3 (VDD), D2.3 (VDD), D3.3 (VDD), D4.3 (VDD), D5.3 (VDD), D6.3 (VDD), D7.3 (VDD), D8.3 (VDD), Q1.3 (D), U4.5 (VCC)
/U0RXD: TP7.1, U1.40 (RXD0)
/U0TXD: TP6.1, U1.39 (TXD0)
/USB_DM: R3.2, U1.23 (IO19)
/USB_DM_C: J1.A7 (DN1), R3.1, U2.3 (I/O2), U2.4 (I/O2)
/USB_DP: R2.2, U1.24 (IO20)
/USB_DP_C: J1.A6 (DP1), R2.1, U2.1 (I/O1), U2.6 (I/O1)
GND: C1.2, C2.2, C3.2, C4.2, C5.2, C6.2, C7.2, C8.2, C9.2, C10.2, C11.2, C12.2, C13.2, C14.2, C15.2, C17.2, D1.1 (GND), D2.1 (GND), D3.1 (GND), D4.1 (GND), D5.1 (GND), D6.1 (GND), D7.1 (GND), D8.1 (GND), J1.25 (GND), J1.26 (GND), J1.A1 (GND), J1.A12 (GND), J1.B1 (GND), J1.B12 (GND), JP1.2 (B), Q2.2 (S), R1.2, R10.2, SW1.4 (D), TP3.1, U1.1 (GND), U1.2 (GND), U1.42 (GND), U1.43 (GND), U1.46 (GND), U1.47 (GND), U1.48 (GND), U1.49 (GND), U1.50 (GND), U1.51 (GND), U1.52 (GND), U1.53 (GND), U1.54 (GND), U1.55 (GND), U1.56 (GND), U1.57 (GND), U1.58 (GND), U1.59 (GND), U1.60 (GND), U1.GND, U2.2 (GND), U3.2 (GND), U4.1 (~OE), U4.3 (GND)
VBUS: C1.1, C2.1, C16.1, J1.A4 (VBUS), J1.A9 (VBUS), J1.B4 (VBUS), J1.B9 (VBUS), Q1.2 (S), R8.1, TP1.1, U2.5 (VBUS), U3.1 (VIN), U3.3 (EN)

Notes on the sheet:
Power flags
USB-C plug, CC and ESD
Direct-attach device: Rd 5.1k on CC asks the host for 5 V. USBLC6 behind the plug, 22R near the module.
3.3 V supply
AP2112K-3.3: 600 mA for a 355 mA Wi-Fi peak. 4.7u + 100n in, 10u out, 4.7u + 100n at the module.
ESP32-S3-MINI-1-N8
8 MB flash, no PSRAM. Antenna at the board end: no copper under it.
Confirmation button
GPIO5, active low, the chip's own pull-up. GPIO0 (BOOT) is only the bottom jumper.
Status ring
8 x SK6805-EC20 on LED_VDD; SN74LV1T125 lifts GPIO6 to a 5 V data swing; 100n at each LED.
Ring power switch
GPIO7 high: Q2 pulls Q1 on. C16 holds it off at plug-in, R9/C16 soften the turn-on; R10 keeps it off until the firmware runs.
Test points (bottom)
Bring-up and the UART console; JP1 shorted = download mode.

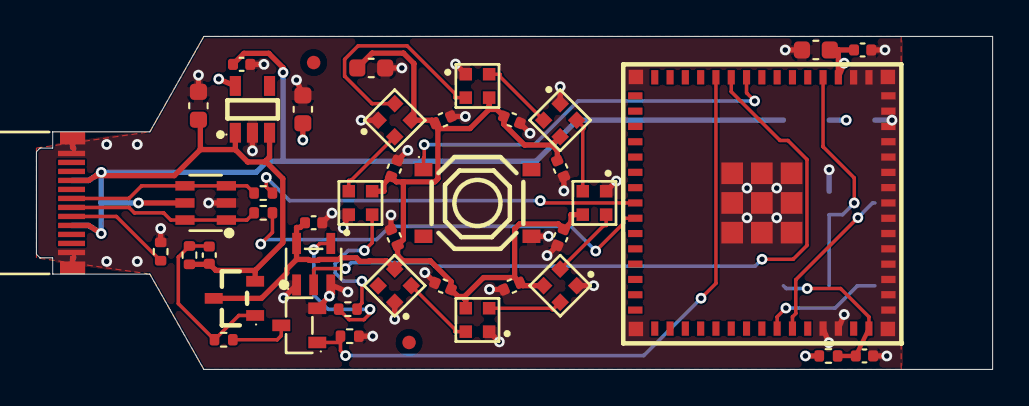
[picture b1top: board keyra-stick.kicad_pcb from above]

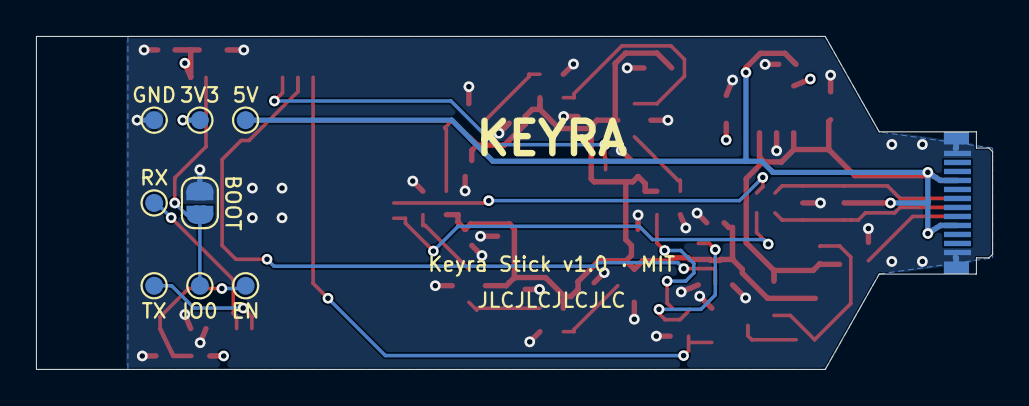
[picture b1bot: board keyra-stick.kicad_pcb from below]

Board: 4 copper layers, 53.1 x 18.5 mm, 51 parts (8 on the bottom side), 27 nets.

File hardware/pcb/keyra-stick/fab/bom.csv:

Comment,Designator,Footprint,LCSC Part #
4.7u,"C1,C15,C17",C_0603_1608Metric,C19666
100n,"C2,C4,C6,C7,C8,C9,C10,C11,C12,C13,C14,C16",C_0402_1005Metric,C1525
10u,C3,C_0603_1608Metric,C19702
1u,C5,C_0402_1005Metric,C52923
SK6805-EC20,"D1,D2,D3,D4,D5,D6,D7,D8",LED-SMD_4P-L2.0-W2.0-TL_J-ST2020RGB-IC-P4-5-SO1,C2890036
USB-C plug,J1,USB-C-SMD_TYPE-C-24P-GTJB-040,C3151751
AO3401A,Q1,SOT-23_L2.9-W1.3-P1.90-LS2.4-BR,C15127
2N7002,Q2,SOT-23-3_L2.9-W1.3-P1.90-LS2.4-BR,C8545
5.1k,R1,R_0402_1005Metric,C25905
22,"R2,R3",R_0402_1005Metric,C25092
330,R6,R_0402_1005Metric,C25104
100k,"R8,R10",R_0402_1005Metric,C25741
10k,"R4,R9",R_0402_1005Metric,C25744
TS-1187A,SW1,SW-SMD_4P-L5.1-W5.1-P3.70-LS6.5-TL_H1.5,C318884
ESP32-S3-MINI-1-N8,U1,BULETM-SMD_ESP32-S3-MINI-1-N8,C2913206
USBLC6-2SC6,U2,SOT-23-6_L2.9-W1.6-P0.95-LS2.8-BL,C7519
AP2112K-3.3,U3,SOT-25-5_L2.9-W1.6-P0.95-LS2.8-BL,C51118
SN74LV1T125,U4,SOT-23-5_L3.0-W1.7-P0.95-LS2.8-BL,C473338
